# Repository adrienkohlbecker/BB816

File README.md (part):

# BB816

A homebrew computer based on the 65C816 processor. Watch the series on YouTube:

## Goals

The purpose of this project is to build a 65C816 development platform and learn about the CPU. Conceptually, it will be similar to WDC's [own development board](https://wdc65xx.com/Single-Board-Computers/w65c816sxb/).

I'm not going for ludicrous speed and features for revision A, here are the goals:

- Runs at 4Mhz
- Prototyped on a breadboard, through-hole ICs only, no programmable logic
- 32KB RAM, 32KB ROM, 512KB extended RAM
- 65C22 for peripheral I/O
- 65C51 for UART

The goals of the YouTube series are to provide a good description of all the design decisions, including going in-depth on timing, to be a more advanced complement to something like Ben Eater's 6502 series, as well as show more love to this cool CPU in the homebrew community.

## Schematic

### Top-level

### CPU breakout

### Address Decoding module

### Memory module

### Debug Clock module

### Debug module

### Monitor module

### GPIO module

### Peripherals module

### Serial module

### Tester module

## BOM

### Basics

- BusBoard BB830 Breadboards
- Hook-Up Wire: [Recommended option](https://www.jameco.com/z/JMS9313-01D-Jameco-Valuepro-22-AWG-6-Color-Solid-Tinned-Copper-Hook-Up-Wire-Assortment-100-Feet_2183752.html)
- Male-to-Male Dupont Wires
- [Dupont Female Connectors](https://www.aliexpress.com/item/4001362869482.html). Use them to replace single connectors and group your cables by 2, 8...
- 10uF Polarized capacitors. Sprinkle one per power rail
- 3mm LEDs with built-in resistors ([Yellow](https://www.digikey.com/product-detail/en/WP710A10YD5V/754-1729-ND/3084212), [Red](https://www.digikey.com/product-detail/en/WP710A10ID5V/754-1721-ND/3084187), [Green](https://www.digikey.com/product-detail/en/WP710A10SGD5V/754-1724-ND/3084201))
- LED Bars with 8 LEDs, various colors ([Red version](https://www.aliexpress.com/item/32315190808.html)), with [9-pin bussed 1k resistors](https://nl.mouser.com/ProductDetail/Bourns/4609M-101-102LF?qs=nFt9sTYf7TDihA0IqmqOVw%3D%3D). I use 1k, 1.5k or 3.3k resistors depending on the color.
- ZIF socket for ROM: [Aries Electronics 28-526-10](https://mouser.com/ProductDetail/Aries-Electronics/28-526-10?qs=WZRMhwwaLl9nHDqf31PyaQ%3D%3D) + [28pin Wire-Wrap socket](https://mouser.com/ProductDetail/Mill-Max/123-43-628-41-001000?qs=IGgAdOvCTsSqORqiKCtp8w%3D%3D)

### CPU Breakout board

**Component Count:** 81

| Refs | Qty | Component | Description |
| ----- | --- | ---- | ----------- |
| C1 | 1 | 220u | Polarized capacitor, small symbol |
| C2, C4, C5, C6, C7, C8, C9, C10, C11, C12, C13, C14, C15, C16, C17, C18, C19 | 17 | 100n | Unpolarized capacitor, small symbol |
| C3 | 1 | 10u | Polarized capacitor, small symbol |
| D1 | 1 | POWER | Light emitting diode, small symbol |
| D2 | 1 | 1N5817 | 20V 1A Schottky Barrier Rectifier Diode, DO-41 |
| J1 | 1 | Barrel_Jack_Switch | DC Barrel Jack with an internal switch |
| J2 | 1 | Conn_02x40_Odd_Even | Generic connector, double row, 02x40, odd/even pin numbering scheme (row 1 odd numbers, row 2 even numbers), script generated (kicad-library-utils/schlib/autogen/connector/) |
| J3 | 1 | Conn_02x18_Odd_Even | Generic connector, double row, 02x18, odd/even pin numbering scheme (row 1 odd numbers, row 2 even numbers), script generated (kicad-library-utils/schlib/autogen/connector/) |
| R1, R2, R3, R5, R11, R17 | 6 | 3.3k | Resistor, small symbol |
| R4, R12, R13, R14, R15 | 5 | 100k | Resistor, small symbol |
| R6, R16 | 2 | 1k | Resistor, small symbol |
| R7, R8, R9, R10 | 4 | 0R | Resistor, small symbol |
| RN1 | 1 | 100k | 8 resistor network, star topology, bussed resistors, small symbol |
| RN2, RN3, RN4 | 3 | 100k | 8 resistor network, star topology, bussed resistors, small symbol |
| RN5 | 1 | 100k | 8 resistor network, star topology, bussed resistors, small symbol |
| SW1 | 1 | RESET | Push button switch, generic, two pins |
| U1 | 1 | 74AHC74 | Dual D Flip-flop, Set & Reset |
| U2 | 1 | 74AHC00 | quad 2-input NAND gate |
| U3 | 1 | 74AC112 | dual JK Flip-Flop, Set & Reset |
| U4 | 1 | W65C816SxP | W65C816S 8/16-bit CMOS General Purpose Microprocessor, DIP-40 |
| U5, U6, U12 | 3 | 74AHC32 | Quad 2-input OR |
| U7 | 1 | 74AHC125 | Quad buffer 3-State outputs |
| U8 | 1 | DS1813-5 |  |
| U9, U14 | 2 | 74HC74 | Dual D Flip-flop, Set & Reset |
| U10 | 1 | 74AHCT245 | Octal BUS Transceivers, 3-State outputs |
| U11 | 1 | 74AHC573 | 8-bit Latch 3-state outputs |
| U13 | 1 | 74AHC02 | quad 2-input NOR gate |
| U15 | 1 | 74AC10 | Triple 3-input NAND |
| U16 | 1 | DS1035-10 | 3-in-1 High–Speed Silicon Delay Line |
| X1 | 1 | 8MHz | Crystal Clock Oscillator, DIP8-style metal package |

### Rest of the computer

**Component Count:** 167

| Refs | Qty | Component | Description |
| ----- | --- | ---- | ----------- |
| BAR1 | 1 | LED-Array-10-BGYR | BAR GRAPH 10 segment |
| BAR2, BAR3, BAR4 | 3 | Yellow | BAR GRAPH 8 segment |
| BAR5 | 1 | Green | BAR GRAPH 8 segment |
| BAR6, BAR7, BAR8 | 3 | Red | BAR GRAPH 8 segment |
| BAR9, BAR10 | 2 | LED-Array-8-GYR | BAR GRAPH 10 segment |
| C1, C6, C10, C27 | 4 | 10u | Polarized capacitor, small symbol |
| C2, C3, C4, C5, C7, C8, C9, C12, C16, C17, C18, C19, C20, C21, C22, C23, C24, C28, C29, C30, C31, C32, C33, C34, C35, C36, C37, C38, C39, C41, C42, C43, C44 | 33 | 100n | Unpolarized capacitor, small symbol |
| C11 | 1 | 22u | Polarized capacitor, small symbol |
| C13, C14, C15 | 3 | 2.2u | Polarized capacitor, small symbol |
| C25 | 1 | 1u | Polarized capacitor, small symbol |
| C26 | 1 | 10n | Unpolarized capacitor, small symbol |
| C40 | 1 | 470n | Unpolarized capacitor, small symbol |
| D1 | 1 | Clock | Light emitting diode, small symbol |
| D2, D7 | 2 | 1N5819 | 40V 1A Schottky Barrier Rectifier Diode, DO-41 |
| D8 | 1 | Slow | Light emitting diode, small symbol |
| D9 | 1 | Fast | Light emitting diode, small symbol |
| D10 | 1 | Pulse | Light emitting diode, small symbol |
| DS1 | 1 | HD44780 | LCD 16x2 Alphanumeric , 8 bit parallel bus, 5V VDD |
| J1 | 1 | Tester | Generic connector, single row, 01x08, script generated (kicad-library-utils/schlib/autogen/connector/) |
| J2 | 1 | USB_B | USB Type B connector |
| J3 | 1 | USB_I2C | Generic connector, single row, 01x04, script generated (kicad-library-utils/schlib/autogen/connector/) |
| J4 | 1 | USB Reset | Generic connector, single row, 01x02, script generated (kicad-library-utils/schlib/autogen/connector/) |
| R1, R9, R10, R11, R12, R13, R14, R15, R19, R20, R34, R35, R36 | 13 | 3.3k | Resistor, small symbol |
| R2, R4, R6, R8 | 4 | 10k | Resistor, small symbol |
| R3, R5, R7 | 3 | 2.2k | Resistor, small symbol |
| R16, R18, R25, R26, R27, R31, R32, R37, R38, R39, R41, R42 | 12 | 1k | Resistor, small symbol |
| R17 | 1 | 220 | Resistor, small symbol |
| R21, R22, R23, R24, R33, R43, R44, R45, R46, R47, R48, R49, R50, R51 | 14 | 6.8k | Resistor, small symbol |
| R28, R29, R30, R40 | 4 | 1.5k | Resistor, small symbol |
| RN1, RN2, RN3 | 3 | 1k | 8 resistor network, star topology, bussed resistors, small symbol |
| RN4, RN7 | 2 | 3.3k | 8 resistor network, star topology, bussed resistors, small symbol |
| RN5, RN6, RN8 | 3 | 1.5k | 8 resistor network, star topology, bussed resistors, small symbol |
| RV1 | 1 | 500k | Potentiometer |
| RV2 | 1 | 10k | Potentiometer |
| SW1 | 1 | Pulse | Push button switch, generic, two pins |
| SW2 | 1 | Mode | Push button switch, generic, two pins |
| SW3 | 1 | Speed | Push button switch, generic, two pins |
| SW4 | 1 | SW_DIP_SPDT_x02 | 2x DIP Switch, Single Pole Double Throw (SPDT) switch, small symbol |
| SW5 | 1 | SW_DIP_x03 | 3x DIP Switch, Single Pole Single Throw (SPST) switch, small symbol |
| SW6 | 1 | SW_DIP_x08 | 8x DIP Switch, Single Pole Single Throw (SPST) switch, small symbol |
| U1 | 1 | 65C816-Breakout | See https://github.com/adrienkohlbecker/BB816/tree/main/hardware/breakout |
| U2 | 1 | 74HC30 | 8-input NAND |
| U3 | 1 | 74AHC00 | quad 2-input NAND gate |
| U4 | 1 | 74AHC32 | Quad 2-input OR |
| U5 | 1 | 74AHC138 | Decoder 3 to 8 active low outputs |
| U6 | 1 | AT28C256-15PC | Paged Parallel EEPROM 256Kb (32K x 8), DIP-28/SOIC-28 |
| U7 | 1 | LY62256PL-55LL | 32Kx8 bit Low Power CMOS Static RAM, 55/70ns, DIP-28 |
| U8 | 1 | AS6C4008-55PCN | 512K x 8 Low Power CMOS RAM, DIP-32 |
| U9 | 1 | 74HC14 | Hex inverter schmitt trigger |
| U10, U12, U14 | 3 | 74HC74 | Dual D Flip-flop, Set & Reset |
| U11 | 1 | 74HC32 | Quad 2-input OR |
| U13 | 1 | 74HCT193 | Synchronous 4-bit Up/Down (2 clk) counter |
| U15, U31 | 2 | 74AHC74 | Dual D Flip-flop, Set & Reset |
| U16 | 1 | LMC555xN | CMOS Timer, 555 compatible, PDIP-8 |
| U17 | 1 | 74HC251 | Multiplexer 8 to 1, 3-state Outputs |
| U18 | 1 | 74HC153 | Dual Multiplexer 4 to 1 |
| U19 | 1 | 74HC04 | Hex Inverter |
| U20 | 1 | 74HC540 | 8-bit Buffer/Line driver Inverter, 3-state outputs |
| U21, U22, U23, U24, U27, U28, U32, U33 | 8 | 74HC541 | 8-bit Buffer/Line Driver 3-state outputs |
| U25 | 1 | Teensy++2.0 |  |
| U26 | 1 | W65C22SxP | W65C22S CMOS Versatile Interface Adapter (VIA), 20-pin I/O, 2 Timer/Counters, DIP-40 |
| U29 | 1 | W65C51NxP | W65C51N CMOS Asynchronous Communication Interface Adapter (ACIA), Serial UART, DIP-28 |
| U30 | 1 | MCP2221AxP | USB to I2C/UART Protocol Converter with GPIO, DIP-14 |
| X1 | 1 | 8MHz | Crystal Clock Oscillator, DIP14-style metal package |
| X2 | 1 | 1.8432MHz | Crystal Clock Oscillator, DIP8-style metal package |

### Used in previous videos

TODO: This hasn't been updated in a while

| Refs | Qty | Component | Description |
| ----- | --- | ---- | ----------- |
| U* | 1 | 74AC08 | Quad And2 |

### Replacement for obsolete chips

- `DS1035-10`: can be replaced by `DS1135Z-10+` with a SOIC-8 to through hole adapter
- `Teensy++ 2.0`: While it is not manufactured by PJRC anymore, clones of this board are available on sites such as Aliexpress

## Memory map

### Diagram

### Decoding

## Timing diagrams

### Clock

<details><summary>View source</summary><p>

Uses [custom fork](https://github.com/adrienkohlbecker/wavedrom)

```js
{
  signal: [
    { name: 'CLK_SRC', wave: '0..(25)x(10)1(40)x(10)0(17)', phase: 0.20 },
    { nodes: ['...(25)Ο(5)Ό(5)G(40)H(5)R(5)P', '...(30)Ν(10)Ά(40)Β(10)Ξ'], phase: 0.45 },
    { name: 'CLK-', wave: '0..(37.5)x(5)1(45)x(5)0..(7.5)', phase: 0.20 },
    { nodes: ['...(37.5)Ё(2.5)Ж(2.5)S(45)T(2.5)Ћ(2.5)Δ', '...(40)L(10)K(40)M(10)Σ'], phase: 0.45 },
    { name: 'CLK', wave: '1.0(50)1(50)0.', phase: 0.20 },
    { nodes: ['..Θ(10)Λ(40)Њ(10)Ќ', '...(7.5)Љ(2.5)Є(2.5)Υ(45)Ю(2.5)Ψ(2.5)Ω'], phase: 0.45 },
    { name: 'CLK+', wave: '1..(7.5)x(5)0(45)x(5)1..(37.5)', phase: 0.20 },
    {},
    { nodes: ['..Ε(8.5)Ι(41.5)Κ(8.5)Μ', '..Ρ(1)Τ(49)Χ(1)А'], phase: 0.45 },
    { name: '~CLK', wave: '0..(1)x(7.5)1(42.5)x(7.5)0..(41.5)', phase: 0.20 },
  ],
  edge: [
    'Ν+Ά 10ns', 'Β+Ξ 10ns', 'Ο+Ό 5ns', 'Ό+G 5ns', 'H+R 5ns', 'R+P 5ns',
    'L+K 10ns', 'M+Σ 10ns', 'Ё+Ж 2.5ns', 'Ж+S 2.5ns', 'T+Ћ 2.5ns', 'Ћ+Δ 2.5ns',
    'Θ+Λ 10ns', 'Њ+Ќ 10ns', 'Љ+Є 2.5ns', 'Є+Υ 2.5ns', 'Ю+Ψ 2.5ns', 'Ψ+Ω 2.5ns',
    'Ε+Ι 8.5ns', 'Κ+Μ 8.5ns', 'Ρ+Τ 1ns', 'Χ+А 1ns'
  ],
  config: {
    skin: 'narrower',
    lines: {
      offset: 2,
      every: 50
    },
    background: 'white',
  },
  head: {
    tick: -2,
    every: 10,
    text: ['tspan', { "font-size": '12px' }, 'based on 10Mhz clock']
  }
}
```
</p></details>

### DB/BA Latch

<details><summary>View source</summary><p>

Uses [custom fork](https://github.com/adrienkohlbecker/wavedrom)

```js
{
  signal: [
    { name: 'CLK', wave: '1.0(125)1(125)0.', phase: 0.20 },
    { nodes: ['..Ѳ(10)Ѵ(115)Ά(10)Β', '...(7.5)Α(2.5)Γ(2.5)Ν(120)Ξ(2.5)Ο(2.5)Ό'], phase: 0.90 },
    { name: 'CLK+', wave: '1..(7.5)x(5)0(120)x(5)1..(112.5)', phase: 0.20 },
    { nodes: ['..B(33)Π', '..A(10)D(115)E(10)F(105)G(10)H'], phase: 0.90 },
    { name: 'CPU D0-D7 (read)', wave: '6..(10)x(23)7(102)x(105)6..(10)', data: ['Rd Data', 'Bank Address', 'Rd Data'], phase: 0.20 },
    { nodes: ['..K(33)C(92)Σ(30)I', '..Ρ(10)L(23)C(92)M(10)N'], phase: 0.90 },
    { name: 'CPU D0-D7 (write)', wave: '6(12)x(23)7(102)x(20)6(97)', data: ['Wr Data', 'Bank Address', 'Write Data'], phase: 0.20 },
    { nodes: ['...(12.5)Я(17)P(95.5)Τ(8.5)S', '...(7.5)J(2)O..(113.5)Q(1)R'], phase: 0.90 },
    { name: '/READ_CLOCK', wave: '0..(9.5)x(20)1(96.5)x(7.5)0(118.5)', node: '..(123.5)É(3.5)È.(6.5)À(1.5)Ç', phase: 0.20, nphase: 0.90, nyoffset: -6 },
    { nodes: ['..(34)Υ(11)Z'], phase: 0.90 },
    { nodes: ['...(33)X(1)Y', '...(9.5)T(1)U(19)V(12)W'], phase: 0.90 },
    { name: 'BA0-BA7', wave: '7..(10.5)x(33.5)7(208)', data: ['BA', 'Bank Address'], phase: 0.20 },
  ],
  edge: [
    'Ѳ+Ѵ 10ns', 'Α+Γ 2.5ns', 'Γ+Ν 2.5ns', 'Ά+Β 10ns', 'Ξ+Ο 2.5ns', 'Ο+Ό 2.5ns',
    'A+D 10ns', 'B+Π 33ns', 'E+F 10ns', 'G+H 10ns',
    'Ρ+L 10ns', 'K+C 33ns', 'M+N 10ns', 'Σ+I 30ns',
    'J+O 2ns', 'Я+P 17ns', 'Q+R 1ns', 'Τ+S 8.5ns',
    'T+U 1ns', 'V+W 12ns', 'X+Y 1ns', 'Υ+Z 11s',
    'É+È 3.5ns', 'À+Ç 1.5ns',
  ],
  config: {
    skin: 'narrowerer',
    lines: {
      offset: 2,
      every: 125
    },
    background: 'white'
  },
  head: {
    tick: -2,
    every: 10,
    text: ['tspan', { "font-size": '12px' }, 'based on 4Mhz clock; assumes BE=RDY=1']
  }
}
```
</p></details>

### DB/BA Buffer

<details><summary>View source</summary><p>

Uses [custom fork](https://github.com/adrienkohlbecker/wavedrom)

```js
{
  signal: [
    { name: 'CLK', wave: '1.0(125)1(125)0.', phase: 0.20 },
    { nodes: ['..Ѳ(10)Ѵ(115)Ά(10)Β', '...(7.5)Α(2.5)Γ(2.5)Ν(120)Ξ(2.5)Ο(2.5)Ό'], phase: 0.9 },
    { name: 'CLK+', wave: '1..(7.5)x(5)0(120)x(5)1..(112.5)', phase: 0.20 },
    { nodes: ['..B(33)Π', '..A(10)D(115)E(10)F(105)G(10)H'], phase: 0.9 },
    { name: 'CPU D0-D7 (read)', wave: '6..(10)x(23)7(102)x(105)6..(10)', data: ['Rd Data', 'Bank Address', 'Rd Data'], phase: 0.20 },
    { nodes: ['..K(33)C(92)Σ(30)I', '..Ρ(10)L(23)C(92)M(10)N'], phase: 0.9 },
    { name: 'CPU D0-D7 (write)', wave: '6(12)x(23)7(102)x(20)6(97)', data: ['Wr Data', 'Bank Address', 'Write Data'], phase: 0.20 },
    { nodes: ['..Ύ(30)Д', '..Б(10)Г'], phase: 0.9 },
    { name: 'AHCT245 DIR', wave: '3..(10)x(20)3(220)..', data: ['RWB', 'RWB'], phase: 0.20 },
    { node: '...(10)Ё(1)Ж(19)З(17.5)И', phase: 0.9 },
    { name: 'AHCT245 OUT', wave: '2..(11)x(36.5)2(202.5)..', data: ['DIR valid', 'DIR valid'], phase: 0.20 },
    { nodes: ['...(11)(2.5)І(16.5)Л(97)(11)(2.5)Ѣ(15)Ц', '...(7.5)Й(2)К(116.5)(7.5)П(2)Ф'], phase: 0.9 },
    { name: 'AHCT245 OE', wave: '0..(9.5)x(19.5)1(105.5)x(18)0(97.5)..', data: ['RWB', 'RWB'], phase: 0.20 },
    { node: '...(9.5)Ч(1)Ш(18.5)Щ(17.5)Ъ(88)Ы(1)Ь(17)Э(17)Ю', phase: 0.9 },
    { name: 'AHCT245 OUT', wave: '2..(10.5)x(36)2(89)x(34)2(80.5)..', data: ['ON', 'OFF', 'ON'], phase: 0.20 },
    { nodes: ['..Ε(10)Δ', '..(10)Φ(1)Έ(219)Ζ(11)Η(10)Ή'], phase: 0.9 },
    { name: 'AHCT245 OUT (read)', wave: '2..(9)x(220)2(21)..', data: ['Rd Data', 'Read Data'], phase: 0.20 },
    { node: '..Θ(10)Ι(1)Ί(114)Κ(30)Λ(11)Μ', phase: 0.9 },
    { name: 'AHCT245 OUT (write)', wave: '2..(11)x(155)2(84)..', data: ['Wr Data', 'Write Data'], phase: 0.20 },
    { nodes: ['..Z(9)R(220)P(21)J'], phase: 0.9 },
    { name: 'D0-D7 (read)', wave: '6..(9)x(220)6(21)..', data: ['Rd Data', 'Read Data'], phase: 0.20 },
    { node: '..T(10.5)Y(114.5)U(44.5)O', phase: 0.9 },
    { name: 'D0-D7 (write)', wave: '6..(10.5)x(159)6(80.5)..', data: ['Wr Data', 'Write Data'], phase: 0.20 },
  ],
  edge: [
    'Ѳ+Ѵ 10ns', 'Α+Γ 2.5ns', 'Γ+Ν 2.5ns', 'Ά+Β 10ns', 'Ξ+Ο 2.5ns', 'Ο+Ό 2.5ns',
    'A+D 10ns', 'B+Π 33ns', 'E+F 10ns', 'G+H 10ns',
    'Ρ+L 10ns', 'K+C 33ns', 'M+N 10ns', 'Σ+I 30ns',
    'Б+Г 10ns', 'Ύ+Д 30ns',
    'Ё+Ж 1ns', 'З+И 17.5ns',
    'Й+К 2ns', 'І+Л 16.5ns', 'П+Ф 2ns', 'Ѣ+Ц 15ns',
    'Ч+Ш 1ns', 'Щ+Ъ 17.5ns', 'Ы+Ь 1ns', 'Э+Ю 17ns',
    'Ε+Δ 10ns', 'Φ+Έ 1ns', 'Ζ+Η 11ns', 'Η+Ή 10ns',
    'Θ+Ι 10ns', 'Ι+Ί 1ns', 'Κ+Λ 30ns', 'Λ+Μ 11ns',
    'Z+R 9ns', 'P+J 21ns', 'T+Y 10.5ns', 'U+O 44.5ns'
  ],
  config: {
    skin: 'narrowerer',
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
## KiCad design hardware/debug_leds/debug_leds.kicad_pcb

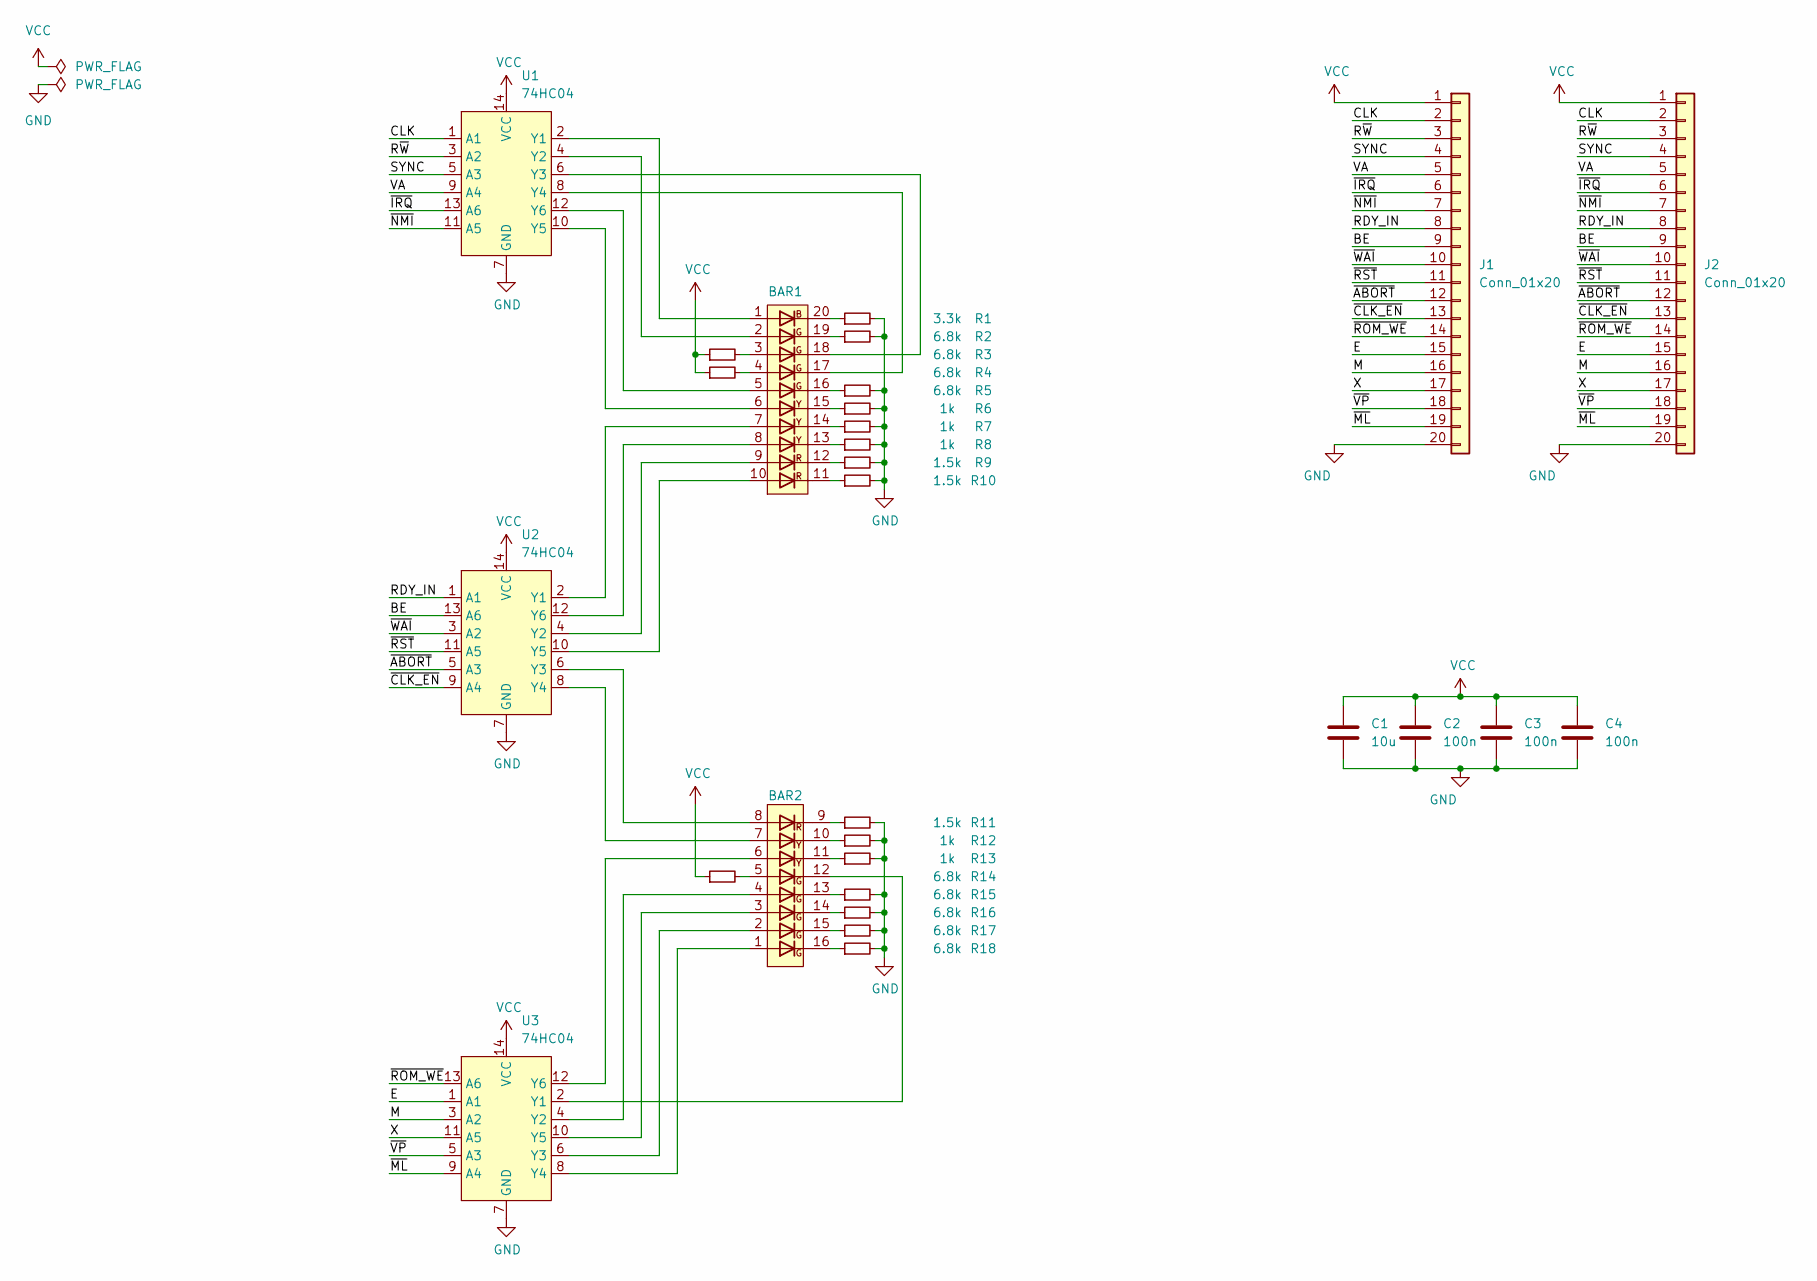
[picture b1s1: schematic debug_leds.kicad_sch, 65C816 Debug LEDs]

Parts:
BAR1: LED-Array-10-BGYR; DIP-20_W7.62mm
BAR2: LED-Array-8-GYR; DIP-16_W7.62mm
C1: 10u; CP_Radial_D4.0mm_P2.00mm
C2, C3, C4: 100n; C_Disc_D3.0mm_W1.6mm_P2.50mm
J1, J2: Conn_01x20; PinHeader_1x20_P2.54mm_Vertical
R1: 3.3k; R_1206_3216Metric_Pad1.30x1.75mm_HandSolder
R2, R3, R4, R5, R14, R15, R16, R17, R18: 6.8k; R_1206_3216Metric_Pad1.30x1.75mm_HandSolder
R6, R7, R8, R12, R13: 1k; R_1206_3216Metric_Pad1.30x1.75mm_HandSolder
R9, R10, R11: 1.5k; R_1206_3216Metric_Pad1.30x1.75mm_HandSolder
U1, U2, U3: 74HC04; DIP-14_W7.62mm

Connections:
/BE: J1.9, J2.9, U2.13 (A6)
/CLK: J1.2, J2.2, U1.1 (A1)
/E: J1.15, J2.15, U3.1 (A1)
/M: J1.16, J2.16, U3.3 (A2)
/RDY_IN: J1.8, J2.8, U2.1 (A1)
/R~W: J1.3, J2.3, U1.3 (A2)
/SYNC: J1.4, J2.4, U1.5 (A3)
/VA: J1.5, J2.5, U1.9 (A4)
/X: J1.17, J2.17, U3.11 (A5)
/~ABORT: J1.12, J2.12, U2.5 (A3)
/~CLK_EN: J1.13, J2.13, U2.9 (A4)
/~IRQ: J1.6, J2.6, U1.13 (A6)
/~ML: J1.19, J2.19, U3.9 (A4)
/~NMI: J1.7, J2.7, U1.11 (A5)
/~ROM_WE: J1.14, J2.14, U3.13 (A6)
/~RST: J1.11, J2.11, U2.11 (A5)
/~VP: J1.18, J2.18, U3.5 (A3)
/~WAI: J1.10, J2.10, U2.3 (A2)
GND: C1.2, C2.2, C3.2, C4.2, J1.20, J2.20, R1.2, R2.2, R5.2, R6.2, R7.2, R8.2, R9.2, R10.2, R11.2, R12.2, R13.2, R15.2, R16.2, R17.2, R18.2, U1.7 (GND), U2.7 (GND), U3.7 (GND)
unnamed: BAR1.3 (A), R3.2
unnamed: BAR1.4 (A), R4.2
unnamed: BAR1.11 (K), R10.1
unnamed: BAR1.12 (K), R9.1
unnamed: BAR1.13 (K), R8.1
unnamed: BAR1.14 (K), R7.1
unnamed: BAR1.15 (K), R6.1
unnamed: BAR1.16 (K), R5.1
unnamed: BAR1.19 (K), R2.1
unnamed: BAR1.20 (K), R1.1
unnamed: BAR2.1 (A), U3.8 (Y4)
unnamed: BAR2.10 (K), R12.1
unnamed: BAR2.11 (K), R13.1
unnamed: BAR2.13 (K), R15.1
unnamed: BAR2.9 (K), R11.1
unnamed: BAR2.5 (A), R14.2
unnamed: BAR2.14 (K), R16.1
unnamed: BAR2.15 (K), R17.1
unnamed: BAR2.16 (K), R18.1
unnamed: BAR1.1 (A), U1.2 (Y1)
unnamed: BAR1.2 (A), U1.4 (Y2)
unnamed: BAR1.18 (K), U1.6 (Y3)
unnamed: BAR1.17 (K), U1.8 (Y4)
unnamed: BAR1.6 (A), U1.10 (Y5)
unnamed: BAR1.5 (A), U1.12 (Y6)
unnamed: BAR1.7 (A), U2.2 (Y1)
unnamed: BAR1.9 (A), U2.4 (Y2)
unnamed: BAR2.8 (A), U2.6 (Y3)
unnamed: BAR2.7 (A), U2.8 (Y4)
unnamed: BAR1.10 (A), U2.10 (Y5)
unnamed: BAR1.8 (A), U2.12 (Y6)
unnamed: BAR2.12 (K), U3.2 (Y1)
unnamed: BAR2.4 (A), U3.4 (Y2)
unnamed: BAR2.2 (A), U3.6 (Y3)
unnamed: BAR2.3 (A), U3.10 (Y5)
unnamed: BAR2.6 (A), U3.12 (Y6)
VCC: C1.1, C2.1, C3.1, C4.1, J1.1, J2.1, R3.1, R4.1, R14.1, U1.14 (VCC), U2.14 (VCC), U3.14 (VCC)

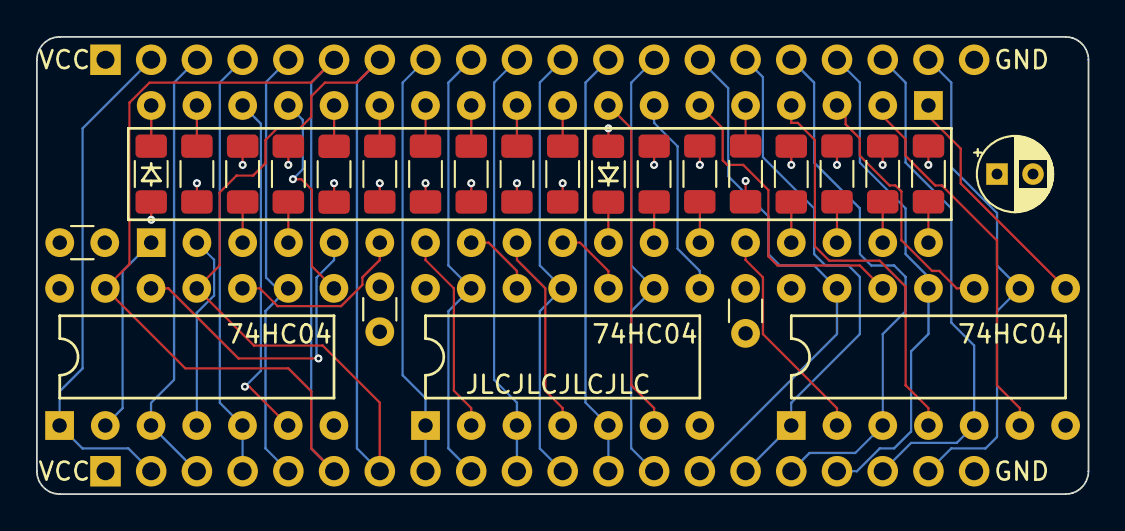
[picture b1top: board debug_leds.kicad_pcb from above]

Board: 4 copper layers, 58.4 x 25.4 mm, 29 parts (0 on the bottom side), 56 nets.

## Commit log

2021-07-20 Schematic start and bank address latching circuit
2021-07-24 Update gitignore patterns
2021-07-24 Don't forget the "C" in 65C816
2021-07-31 Add data pins buffer and pull downs
2021-08-08 Add Bus Enable to the logic for data bus buffer & bank address latch
2021-08-20 Add pull up/down resistors, project symbol library
2021-08-20 Add BOM
2021-09-03 Update for episode 5
2021-09-27 Update for episode 6
2021-09-27 Add timing diagrams
2021-10-21 Timing updates
2021-10-21 Updates for episode 7
2021-10-22 Add thumbnails
2021-10-22 Update bus enable timing diagram
2021-10-23 Update timing diagrams
2021-10-23 Add note on obsolete chips
2021-10-25 Add RDY timing
2021-11-09 Updates for episode 8
2021-11-14 Update gitignore from GitHub
2021-11-16 Updates for episode 9
2021-11-19 Add basics BOM
2021-11-24 Update for episode 10
2021-11-24 Add playlist link
2021-11-24 Add goals
2021-11-24 Update for ep 11
2021-11-24 Re-number parts
2021-11-24 Add version info
2021-11-29 More episode 11 updates
2021-12-01 More updates for ep 11
2021-12-10 Updates for Episode 12
2021-12-14 Annotate tester
2022-01-03 Update to KiCad 6
2022-01-13 Updates for Episode 13
2022-01-13 Update changes
2022-01-15 Updates for Episode 14
2022-01-15 More episode 14 updates
2022-01-16 Fix address sim
2022-01-16 Add address timing
2022-01-16 Add ROM info
2022-01-16 Fix gitignore
2022-01-16 Fix gate
2022-01-16 FIx tester
2022-01-16 More updates for episode 14
2022-01-16 Remove submodule
2022-01-26 Cleanup
2022-01-26 Start episode 15
2022-01-28 Update for Episode 15
2022-02-01 Update for Episode 16
2022-02-01 Update timings
2022-02-01 Add simulation readme
2022-02-01 Update schematics
2022-02-03 More episode 16 updates
2022-02-18 Updates for episode 17
2022-02-24 Update for episode 18
2022-03-02 Update for episode 19
2022-03-07 More episode 19 updates
2022-03-20 More updates for Episode 19
2022-03-28 Update for episode 20
2022-04-01 Updates for episode 20
2022-04-18 Fix monitor output
2022-04-18 Update for episode 21
2022-04-19 Renumber
2022-05-01 More episode 21 update
2022-05-23 Updates for episode 22
2022-05-23 Update for episode 23
2022-07-12 Snapshot ep 24 work
2022-07-20 More updates
2022-07-29 Updates for episode 25
2022-07-29 breakout project
2022-07-30 Update main project
2022-07-30 More updates for episode 25
2022-07-30 Test
2022-07-30 Episode 25
2022-08-01 Fix simulation
2022-08-01 Rename SRC
2022-08-01 Move breakout to single sheet
2022-08-01 Footprints
2022-08-20 Update breakout
2022-09-01 Update gerbers
2022-09-04 Prep ep 28
2022-09-04 Tracing command
2022-09-04 Add Intel Hex decoding
2022-09-04 Add PIN and PORT registers
2022-09-04 Better checksum error
2022-09-04 Byte programming
2022-09-04 tWPH is 50
2022-09-04 Implement data polling
2022-09-04 Add bin2hex and eeprom programming to Makefile
2022-09-10 Refactor
2022-09-10 Add wait
2022-09-25 Prep ep 29
2022-10-21 Add 65C51
2022-10-21 Add ACIA lib
2022-10-21 Polled ACIA
2022-10-21 Refactor main
2022-10-21 Fix timing
2022-10-21 Update acia lib
2022-10-21 Update serial schematic
2022-10-21 Working echo mode
2022-10-21 Fix serial bug
2022-10-21 ACIA timing
2022-10-23 Episode 30
2022-10-23 Update for ep 30
2022-11-09 Add reset from monitor
2022-11-09 Improve EEPROM makefile section
2022-11-09 Clean
2022-11-09 Update via
2022-11-09 Switch to toggle bit
2022-11-09 Implement verification
2022-11-09 Support write protect of EEPROM
2023-01-19 Show Teensy output during programming
2023-01-19 Don't print report
2023-01-20 Update RDY timing
2023-02-06 Update makefile
2023-02-06 Add ROM checksum
2023-02-06 Add delay macros
2023-02-07 Add memory diagnostic
2023-05-09 Episode 31
2023-05-14 Switch monitor to PlatformIO
2023-05-14 Trace optimizations
2023-05-14 Add printing mnemonics
2023-05-14 Update kicad
2023-05-14 refactor main loop
2023-05-14 Update monitor with messages
2023-05-14 Update schematic
2023-05-14 Rename
2023-05-14 Fix assembler warnings
2023-05-14 Default VIA to output low for blank LEDs
2023-05-14 Update for Episode 32
2023-05-14 Episode 32
2023-05-14 Fix macros
2023-05-23 Fix BOM
2023-05-23 Update thumbnails
2023-08-10 Add breakpoint
2023-08-10 Enable s for start stepping
2023-08-10 Fix hexDigitToNumber with lowercase input
2023-08-10 Kicad 7
2023-08-10 Add debug LEDs PCB
2023-08-10 Next ep code
2023-08-10 Update debug leds
2023-08-10 Ep 33
2023-08-10 Move trace processing to host computer
2023-08-10 Add ACIA rx interrupt
2023-08-10 Add binhex
2023-08-10 Fix for supermon
2023-08-10 Move programs to own directory
2023-08-10 ACIA tx irq
2023-08-10 Add march test
2023-08-10 Don't run POST for now
2023-08-10 Separate logging and tracing
2023-08-10 Speed up tracing with buffer
2023-08-10 Load programs in emulation mode
2023-08-10 Add numerical baud rate setting
2023-08-10 Reserve space for I/O expansion
2023-08-15 Add supermon816 source
2023-08-15 Refactor delay loop
2023-08-15 Port supermon816 to ACME
2023-08-15 Add supermon
2023-08-15 Add acia_print_hex
2023-08-15 Support both acia sync and async depending on IRQ flag
2023-08-15 Update supermon with fix for getbyte

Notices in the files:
hardware/debug_leds/debug_leds.kicad_pcb:
Licensed under CERN-OHL-W v2
Copyright © 2022 Adrien Kohlbecker
